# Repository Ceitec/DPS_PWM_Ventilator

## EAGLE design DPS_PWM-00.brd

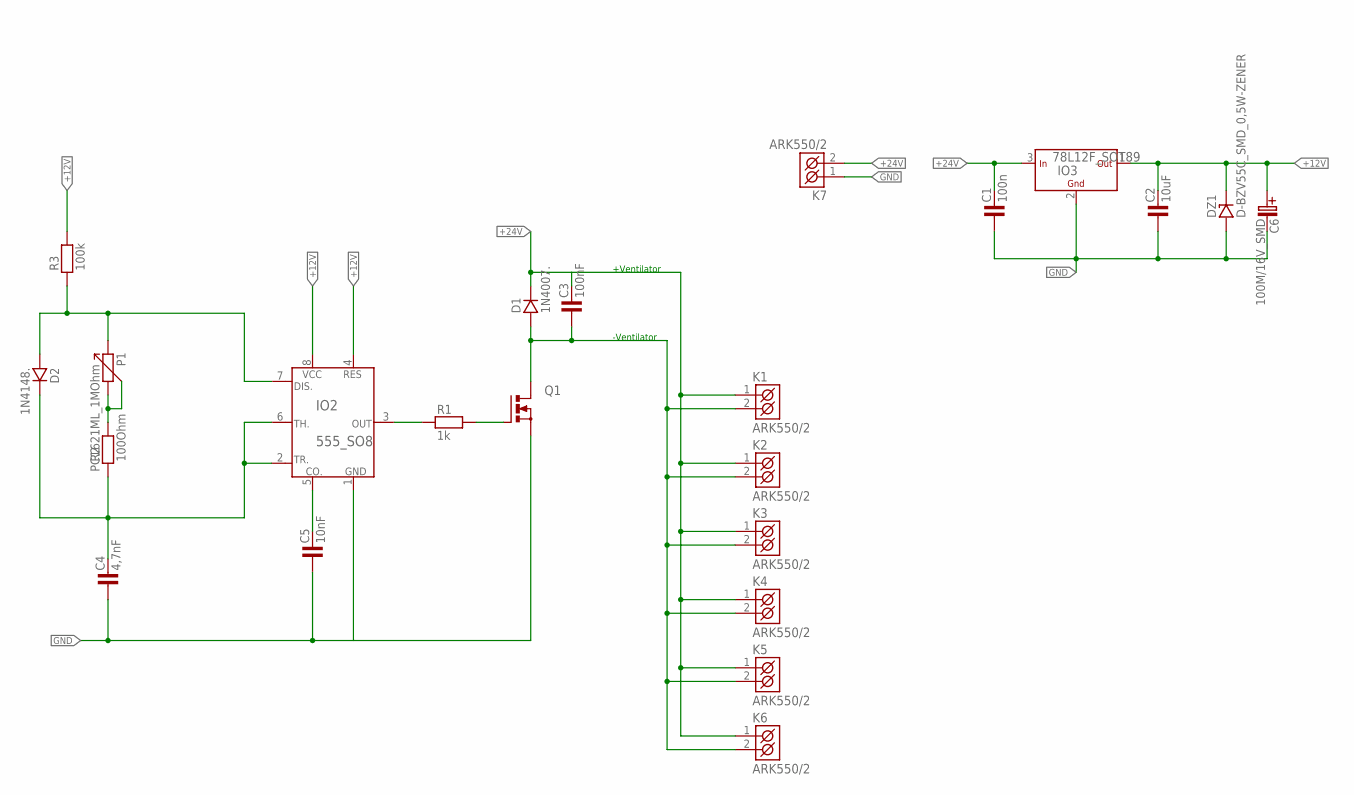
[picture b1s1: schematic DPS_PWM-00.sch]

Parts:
C1: 100n; 1206
C2: 10uF; 1206
C3: 100nF; 1206
C4: 4,7nF; 1206
C5: 10nF; 1206
C6: 100M/16V_SMD; C_EL-SMD_D
D1: 1N4007.; SM-1
D2: 1N4148.; SOD-80
DZ1: D-BZV55C_SMD_0,5W-ZENER; SOD-80
IO2: 555_SO8; SO08
IO3: 78L12F_SOT89; SOT-89
K1, K2, K3, K4, K5, K6, K7: ARK550/2
P1: PC1621ML_1MOhm; PC16ML
Q1: PMOSFET_NTO220BH; TO220BH
R1: 1k; 1206
R2: 100Ohm; 1206
R3: 100k; 1206

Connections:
+12V: C2.2, C6.+ (C_EL+), DZ1.K, IO2.4 (RES), IO2.8 (VCC), IO3.1 (OUT), R3.2
+24V: C1.2, C3.2, D1.K, IO3.3 (IN), K1.1 (K1), K2.1 (K1), K3.1 (K1), K4.1 (K1), K5.1 (K1), K6.1 (K1), K7.2 (K2)
GND: C1.1, C2.1, C4.1, C5.1, C6.- (C_EL-), DZ1.A, IO2.1 (GND), IO3.2 (GND), K7.1 (K1), Q1.S
unnamed: C4.2, D2.K, IO2.2 (TR.), IO2.6 (TH.), R2.1
unnamed: P1.2, P1.3, R2.2
unnamed: D2.A, IO2.7 (DIS.), P1.1, R3.1
unnamed: C5.2, IO2.5 (CO.)
unnamed: Q1.G, R1.2
unnamed: IO2.3 (OUT), R1.1
unnamed: C3.1, D1.A, K1.2 (K2), K2.2 (K2), K3.2 (K2), K4.2 (K2), K5.2 (K2), K6.2 (K2), Q1.D

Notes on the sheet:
+Ventilator
-Ventilator

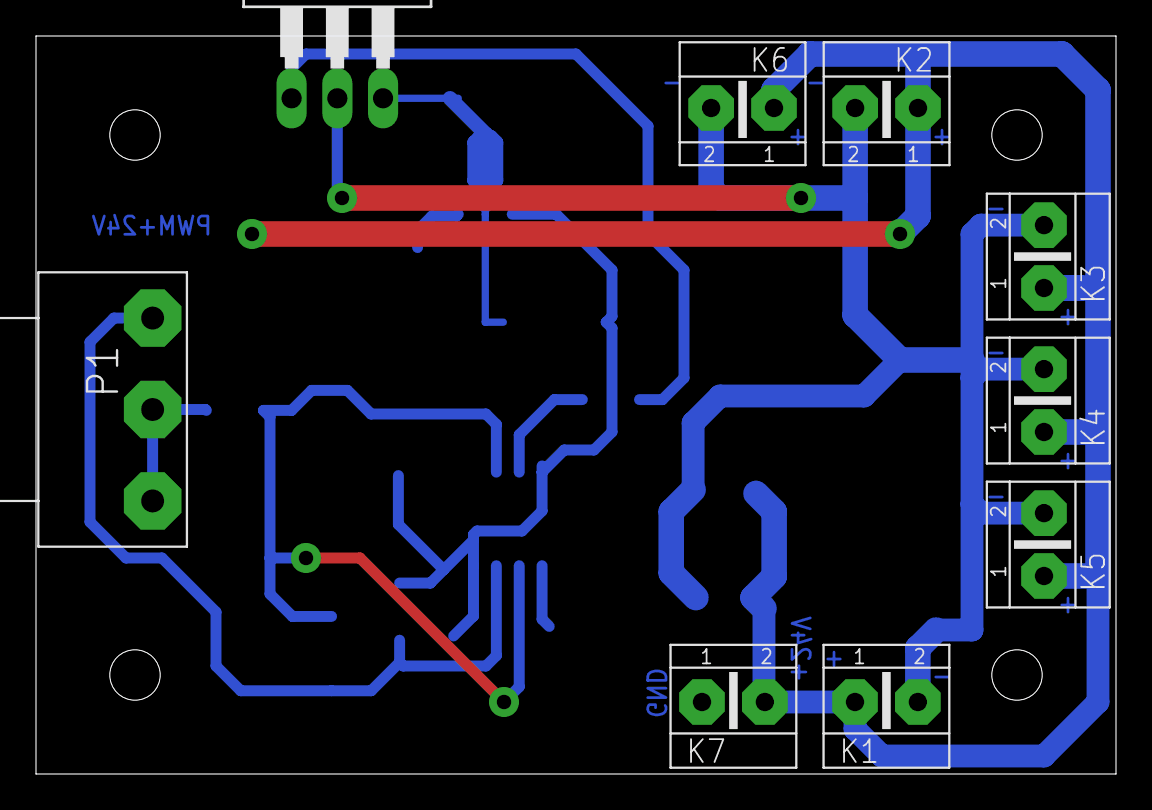
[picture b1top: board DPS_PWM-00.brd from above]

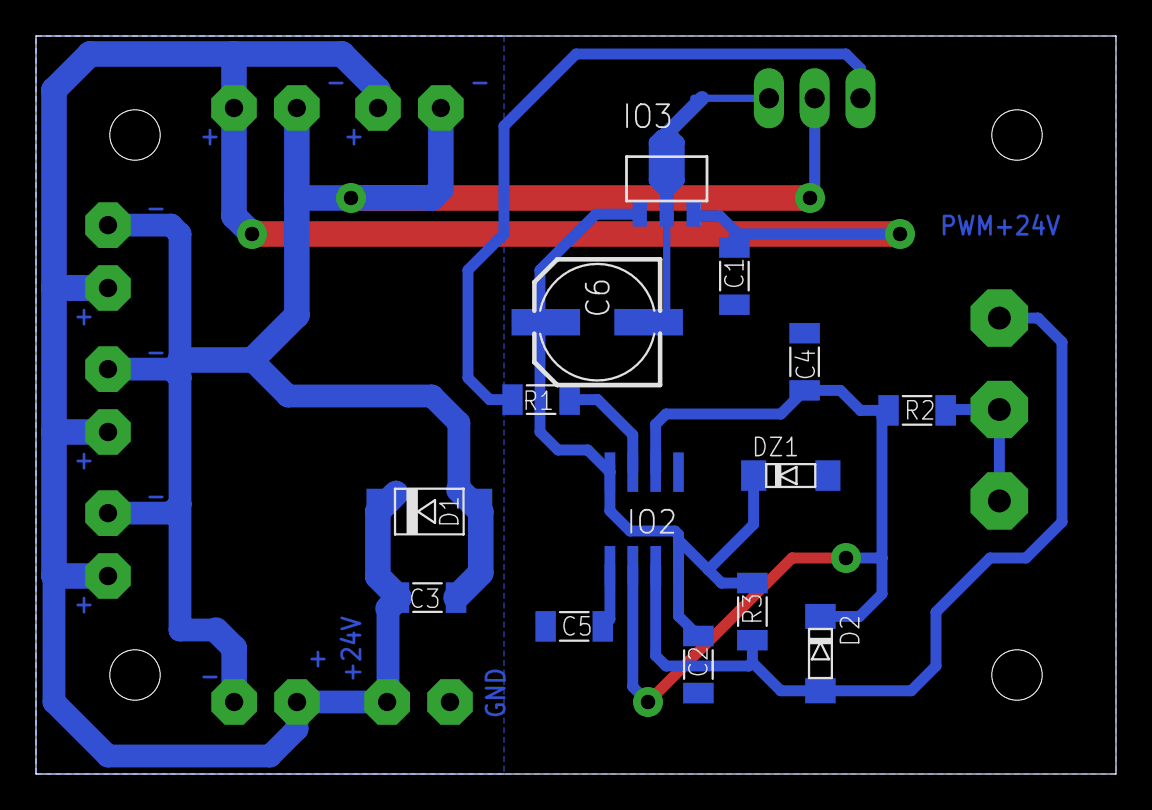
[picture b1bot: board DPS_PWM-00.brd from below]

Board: 2 copper layers, 60.0 x 41.0 mm, 23 parts (14 on the bottom side), 10 nets.

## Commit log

2015-09-07 :lollipop: Added .gitattributes & .gitignore files
2015-09-07 Pridany soubory

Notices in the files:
parts and their libraries:
Copyright (C) PaJa 2001-2014
Copyright (C) PaJa 2003-2009
Copyright (C) PaJa 2011-2014
